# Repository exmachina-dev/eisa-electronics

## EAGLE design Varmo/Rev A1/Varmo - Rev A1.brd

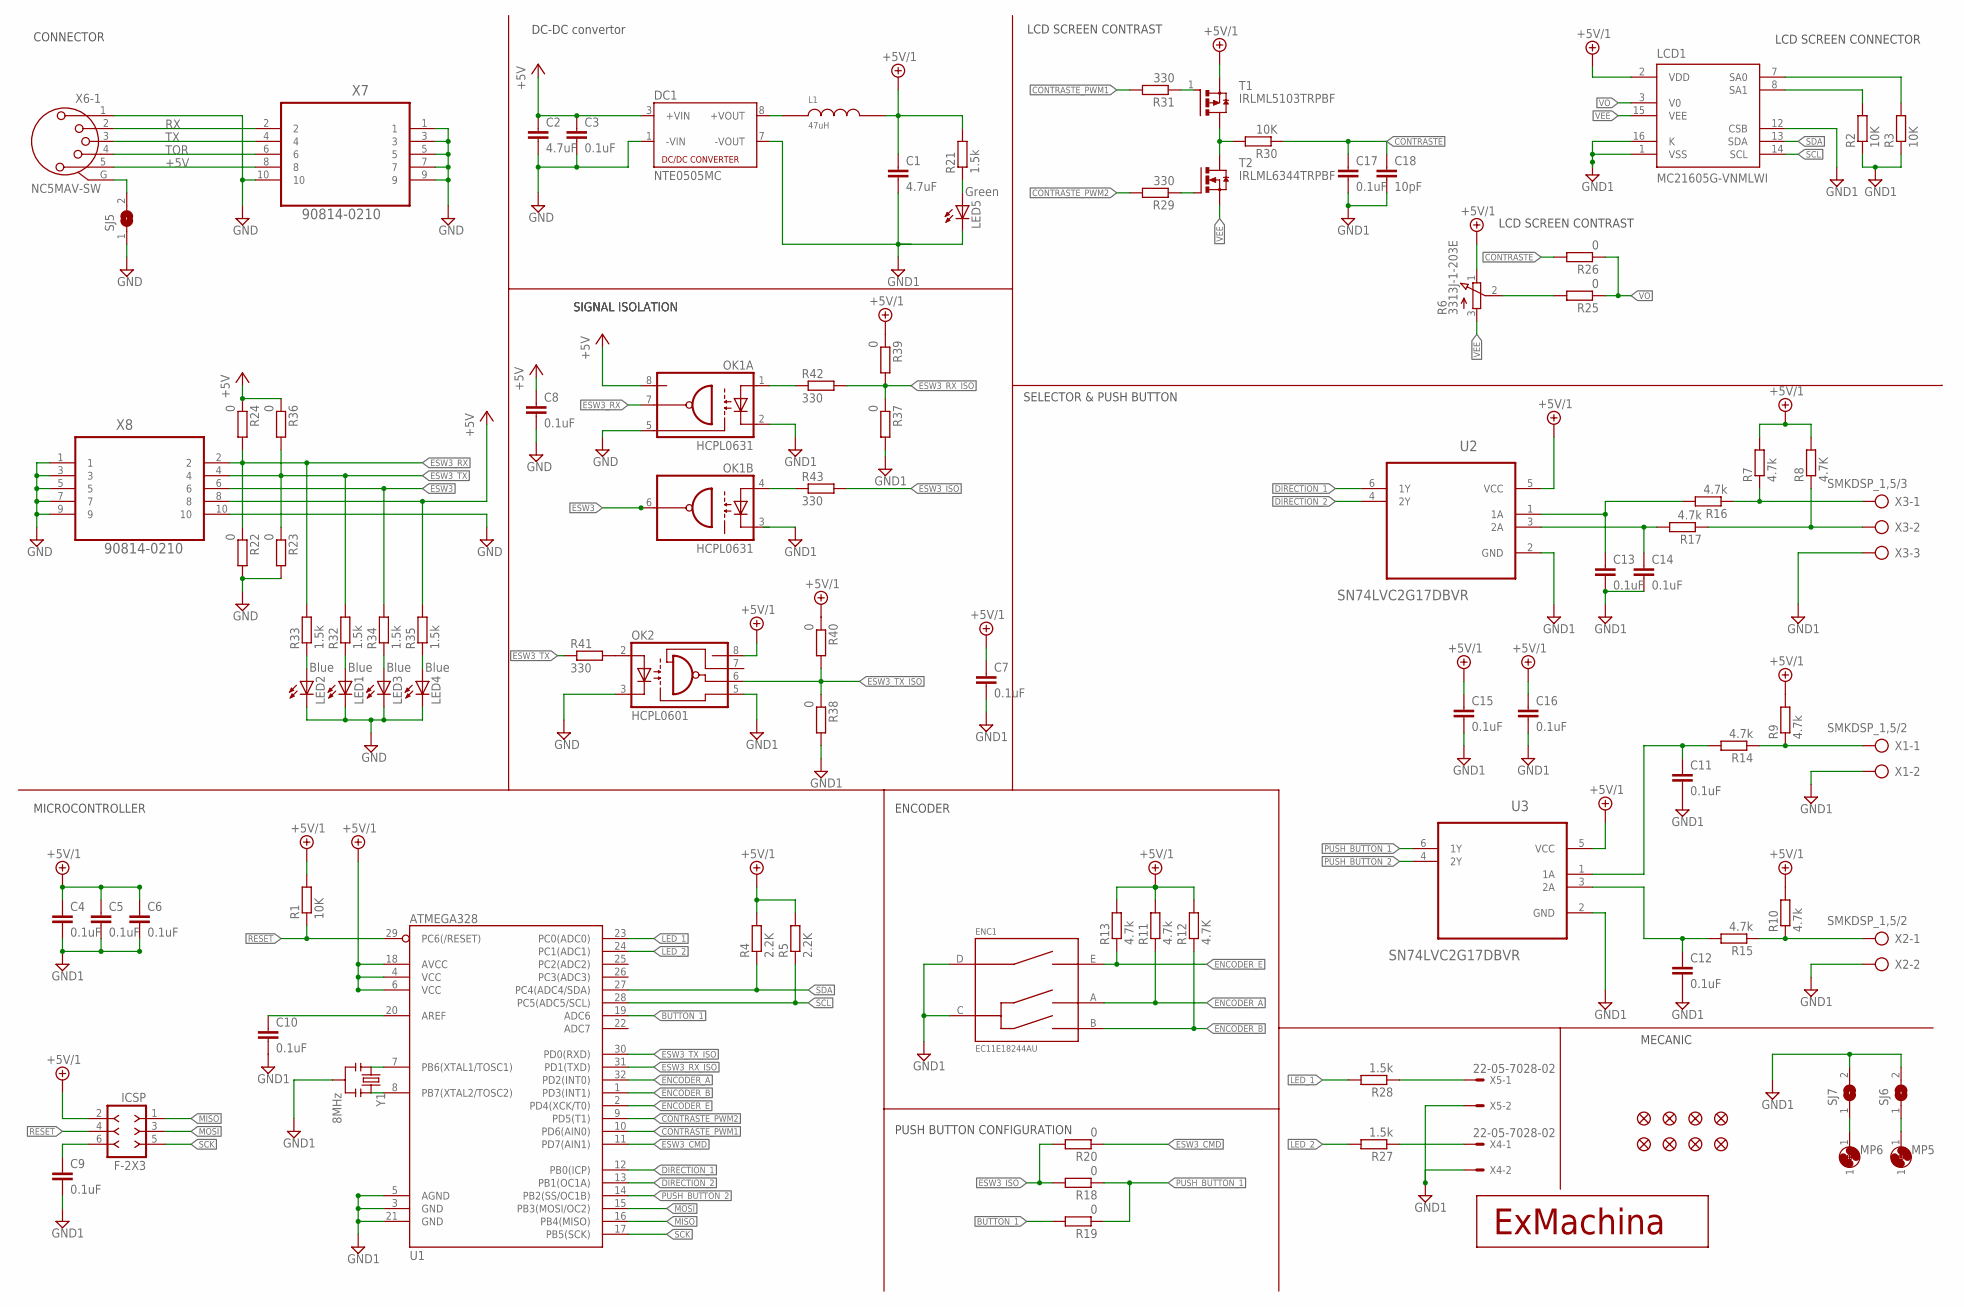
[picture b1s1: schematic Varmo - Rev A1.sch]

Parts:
C1, C2: 4.7uF; C0603; MPN MC0603X475K100CT
C3, C4, C5, C6, C7, C8, C9, C10, C11, C12, C13, C14, C15, C16, C17: 0.1uF; C0603; MPN MC0603B104K160CT
C18: 10pF; C0603; MPN MC0603N100F500CT
DC1: NTE0505MC; NTE; MPN NTE0505MC
ENC1: EC11E18244AU; EC11E
ICSP: F-2X3; DIL-100-2X3; MPN 2213S-06G
JP3, JP4, JP5, JP6, JP7, JP8, JP9, JP10: FIDUCIAL1X2; FIDUCIAL-1X2
L1: 47uH; 8200; MPN 82473C
LCD1: MC21605G-VNMLWI; MC21605G; MPN MC21605G12W-VNMLWI
LED1, LED2, LED3, LED4: Blue; CHIP-LED0603; MPN OVS-0603
LED5: Green; CHIP-LED0603; MPN OVS-0604
MP5, MP6: MOUNT-PAD2.5; P2.5
OK1: HCPL0631; SOIC08
OK2: HCPL0601; SOIC08
R1, R2, R3, R30: 10K; R0603; MPN MCMR06X1002FTL
R4, R5: 2.2K; R0603; MPN MCMR06X2201FTL
R6: 3313J-1-203E; 3313J; MPN 3313J-1-203E
R7, R9, R10, R11, R13, R14, R15, R16, R17: 4.7k; R0603; MPN MCMR06X4701FTL
R8, R12: 4.7K; R0603; MPN MCMR06X4701FTL
R18, R19, R20, R22, R23, R24, R25, R26, R36, R37, R38, R39, R40: 0; R0603; MPN MCMR06X000 PTL
R21, R27, R28, R32, R33, R34, R35: 1.5k; R0603; MPN MCMR06X1501FTL
R29, R31: 330; R0603; MPN MCMR06X3300FTL
R41, R42, R43: 330; R0603; MPN MCMR06X000 PTL
SJ5, SJ6, SJ7: SJ
T1: IRLML5103TRPBF; SOT95P240X112-3N; MPN IRLML5103TRPBF
T2: IRLML6344TRPBF; SOT95P240X112-3N
U1: ATMEGA328; TQFP32-08; MPN ATMEGA328P-AUR
U2, U3: SN74LVC2G17DBVR; SOT95P280X145-6N
U$6: EXMACHINA-LOGO-NAME; EXM-LOGO-BASELINE
X1, X2: SMKDSP_1,5/2
X3: SMKDSP_1,5/3
X4, X5: 22-05-7028-02; 7395-02; MPN 22-05-7028
X6: NC5MAV-SW
X7, X8: 90814-0210; MOLEX_90814-0210
Y1: 8MHz; RESONATOR-SMD; MPN CSTCE8M00G55Z-R0

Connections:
+5V: C2.1, C3.1, C8.1, DC1.3 (+VIN), OK1.8 (VCC), R24.1, R35.2, R36.1, X6.5, X7.8, X8.8
+5V/1: C1.1, C4.1, C5.1, C6.1, C7.1, C15.1, C16.1, ICSP.2, L1.2, LCD1.2 (VDD), OK2.8 (VCC), R1.2, R4.2, R5.2, R6.1 (E), R7.2, R8.2, R9.2, R10.2, R11.2, R12.2, R13.2, R21.2, R39.1, R40.1, T1.2 (S), U1.4 (VCC), U1.6 (VCC), U1.18 (AVCC), U2.5 (VCC), U3.5 (VCC)
BUTTON_1: R19.2, U1.19 (ADC6)
CONTRASTE: C17.1, C18.1, R26.2, R30.1
CONTRASTE_PWM1: R31.2, U1.10 (PD6(AIN0))
CONTRASTE_PWM2: R29.2, U1.9 (PD5(T1))
DIRECTION_1: U1.12 (PB0(ICP)), U2.6 (1Y)
DIRECTION_2: U1.13 (PB1(OC1A)), U2.4 (2Y)
ENCODER_A: ENC1.A, R11.1, U1.32 (PD2(INT0))
ENCODER_B: ENC1.B, R12.1, U1.1 (PD3(INT1))
ENCODER_E: ENC1.E, R13.1, U1.2 (PD4(XCK/T0))
ESW3: OK1.6 (VO2), R34.2, X8.6
ESW3_CMD: R20.1, U1.11 (PD7(AIN1))
ESW3_ISO: R18.2, R20.2, R43.2
ESW3_RX: OK1.7 (VO), R22.1, R24.2, R33.2, X8.2
ESW3_RX_ISO: R37.1, R39.2, R42.2, U1.31 (PD1(TXD))
ESW3_TX: R23.1, R32.2, R36.2, R41.1, X8.4
ESW3_TX_ISO: OK2.6 (VO), R38.1, R40.2, U1.30 (PD0(RXD))
GND: C2.2, C3.2, C8.2, DC1.1 (-VIN), LED1.C, LED2.C, LED3.C, LED4.C, OK1.5 (GND), OK2.3 (C), R22.2, R23.2, SJ5.1, X6.1, X7.1, X7.3, X7.5, X7.7, X7.9, X7.10, X8.1, X8.3, X8.5, X8.7, X8.9, X8.10
GND1: C1.2, C4.2, C5.2, C6.2, C7.2, C9.2, C10.2, C11.2, C12.2, C13.2, C14.2, C15.2, C16.2, C17.2, C18.2, DC1.7 (-VOUT), ENC1.C, ENC1.D, LCD1.1 (VSS), LCD1.12 (CSB), LCD1.16 (K), LED5.C, OK1.2 (C1), OK2.5 (GND), R2.1, R3.1, R37.2, R38.2, SJ6.2, SJ7.2, U1.3 (GND), U1.5 (AGND), U1.21 (GND), U2.2 (GND), U3.2 (GND), X1.2, X2.2, X3.3, X4.2, X5.2, Y1.2
LED_1: R28.2, U1.23 (PC0(ADC0))
LED_2: R27.2, U1.24 (PC1(ADC1))
MISO: ICSP.1, U1.16 (PB4(MISO))
MOSI: ICSP.3, U1.15 (PB3(MOSI/OC2))
unnamed: DC1.8 (+VOUT), L1.1
unnamed: U1.7 (PB6(XTAL1/TOSC1)), Y1.1
unnamed: U1.8 (PB7(XTAL2/TOSC2)), Y1.3
unnamed: C9.1, ICSP.6
unnamed: C10.1, U1.20 (AREF)
unnamed: R10.1, R15.1, X2.1
unnamed: R9.1, R14.1, X1.1
unnamed: R7.1, R16.1, X3.1
unnamed: R8.1, R17.1, X3.2
unnamed: C13.1, R16.2, U2.1 (1A)
unnamed: C14.1, R17.2, U2.3 (2A)
unnamed: C12.1, R15.2, U3.3 (2A)
unnamed: C11.1, R14.2, U3.1 (1A)
unnamed: R6.2 (S), R25.2
unnamed: R27.1, X4.1
unnamed: R28.1, X5.1
unnamed: R29.1, T2.1 (G)
unnamed: R30.2, T1.3 (D), T2.3 (D)
unnamed: SJ5.2, X6.G
unnamed: R31.1, T1.1 (G)
unnamed: LCD1.8 (SA1), R2.2
unnamed: LCD1.7 (SA0), R3.2
unnamed: LED1.A, R32.1
unnamed: LED2.A, R33.1
unnamed: LED3.A, R34.1
unnamed: LED4.A, R35.1
unnamed: LED5.A, R21.1
unnamed: OK1.1 (A1), R42.1
unnamed: OK1.4 (A2), R43.1
unnamed: OK2.2 (A), R41.2
unnamed: MP5.1, SJ6.1
unnamed: MP6.1, SJ7.1
PUSH_BUTTON_1: R18.1, R19.1, U3.6 (1Y)
PUSH_BUTTON_2: U1.14 (PB2(SS/OC1B)), U3.4 (2Y)
RESET: ICSP.4, R1.1, U1.29 (PC6(/RESET))
RX: X6.2, X7.2
SCK: ICSP.5, U1.17 (PB5(SCK))
SCL: LCD1.14 (SCL), R5.1, U1.28 (PC5(ADC5/SCL))
SDA: LCD1.13 (SDA), R4.1, U1.27 (PC4(ADC4/SDA))
TOR: X6.4, X7.6
TX: X6.3, X7.4
VEE: LCD1.15 (VEE), R6.3 (A), T2.2 (S)
VO: LCD1.3 (V0), R25.1, R26.1

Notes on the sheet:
LCD SCREEN CONNECTOR
SIGNAL ISOLATION
DC-DC convertor
LCD SCREEN CONTRAST
MICROCONTROLLER
ENCODER
PUSH BUTTON CONFIGURATION
MECANIC
SELECTOR & PUSH BUTTON
CONNECTOR

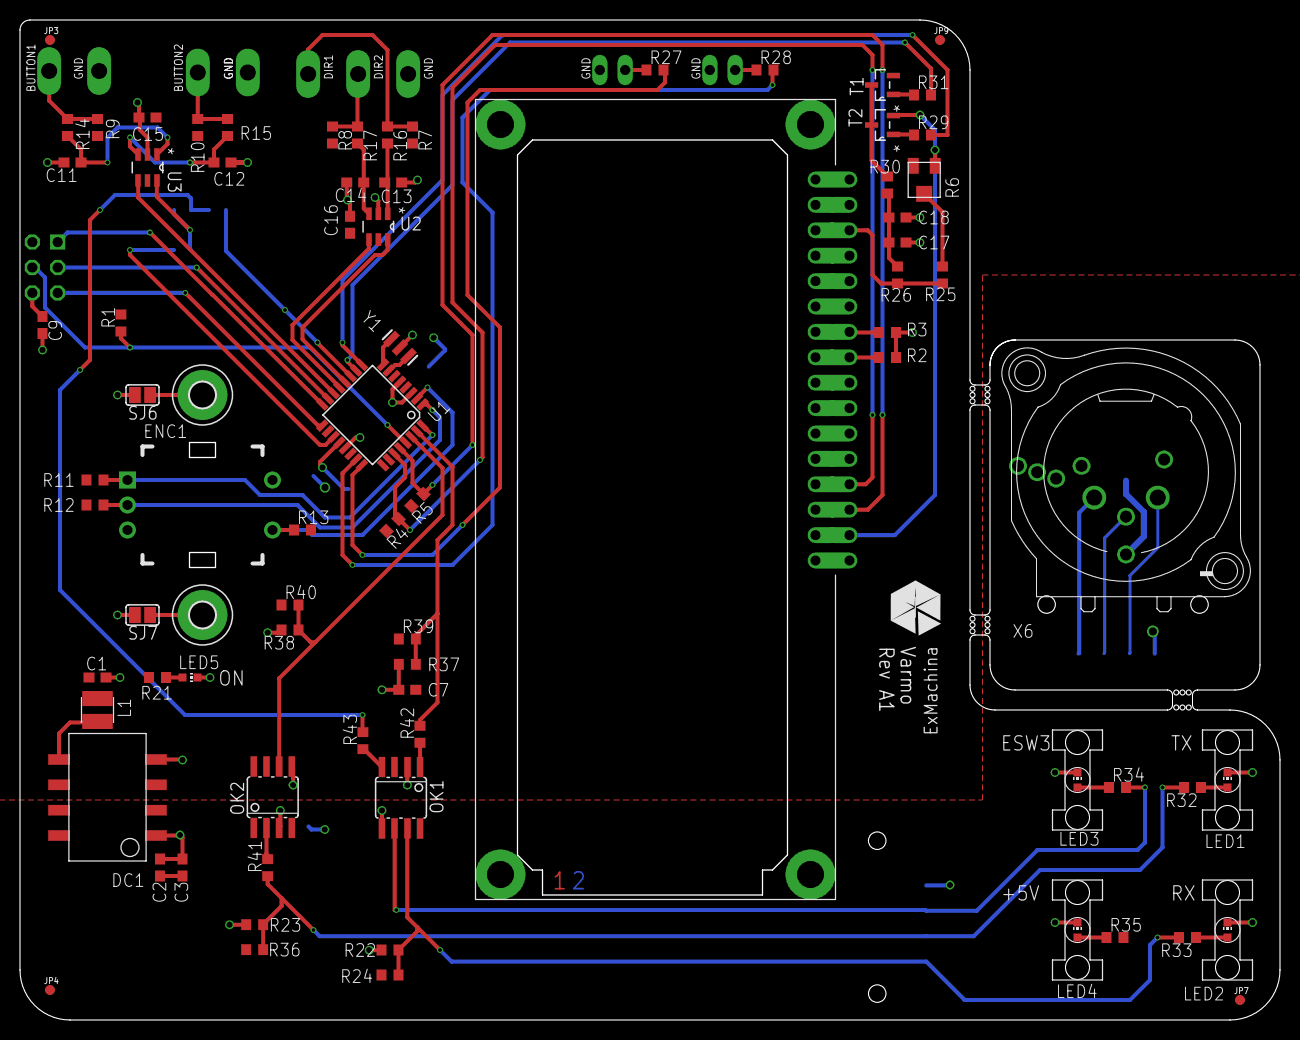
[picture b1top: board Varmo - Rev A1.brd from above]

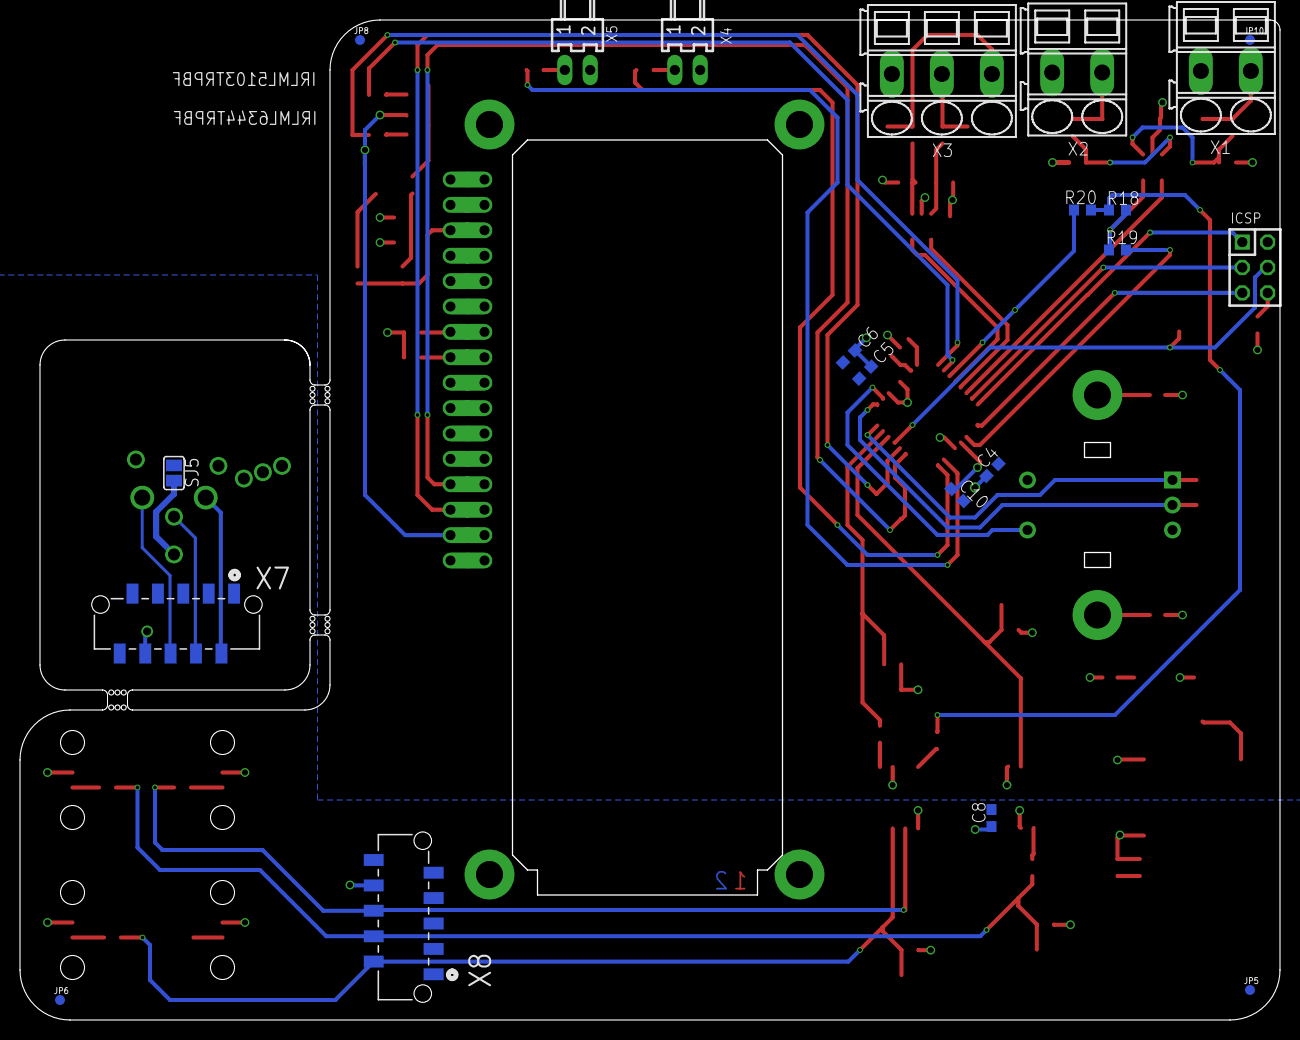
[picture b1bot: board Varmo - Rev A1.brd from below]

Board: 2 copper layers, 126.0 x 100.0 mm, 106 parts (21 on the bottom side), 67 nets.

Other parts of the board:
U$1: A4L-LOC
U$2, U$3, U$4, U$5: 1275.100

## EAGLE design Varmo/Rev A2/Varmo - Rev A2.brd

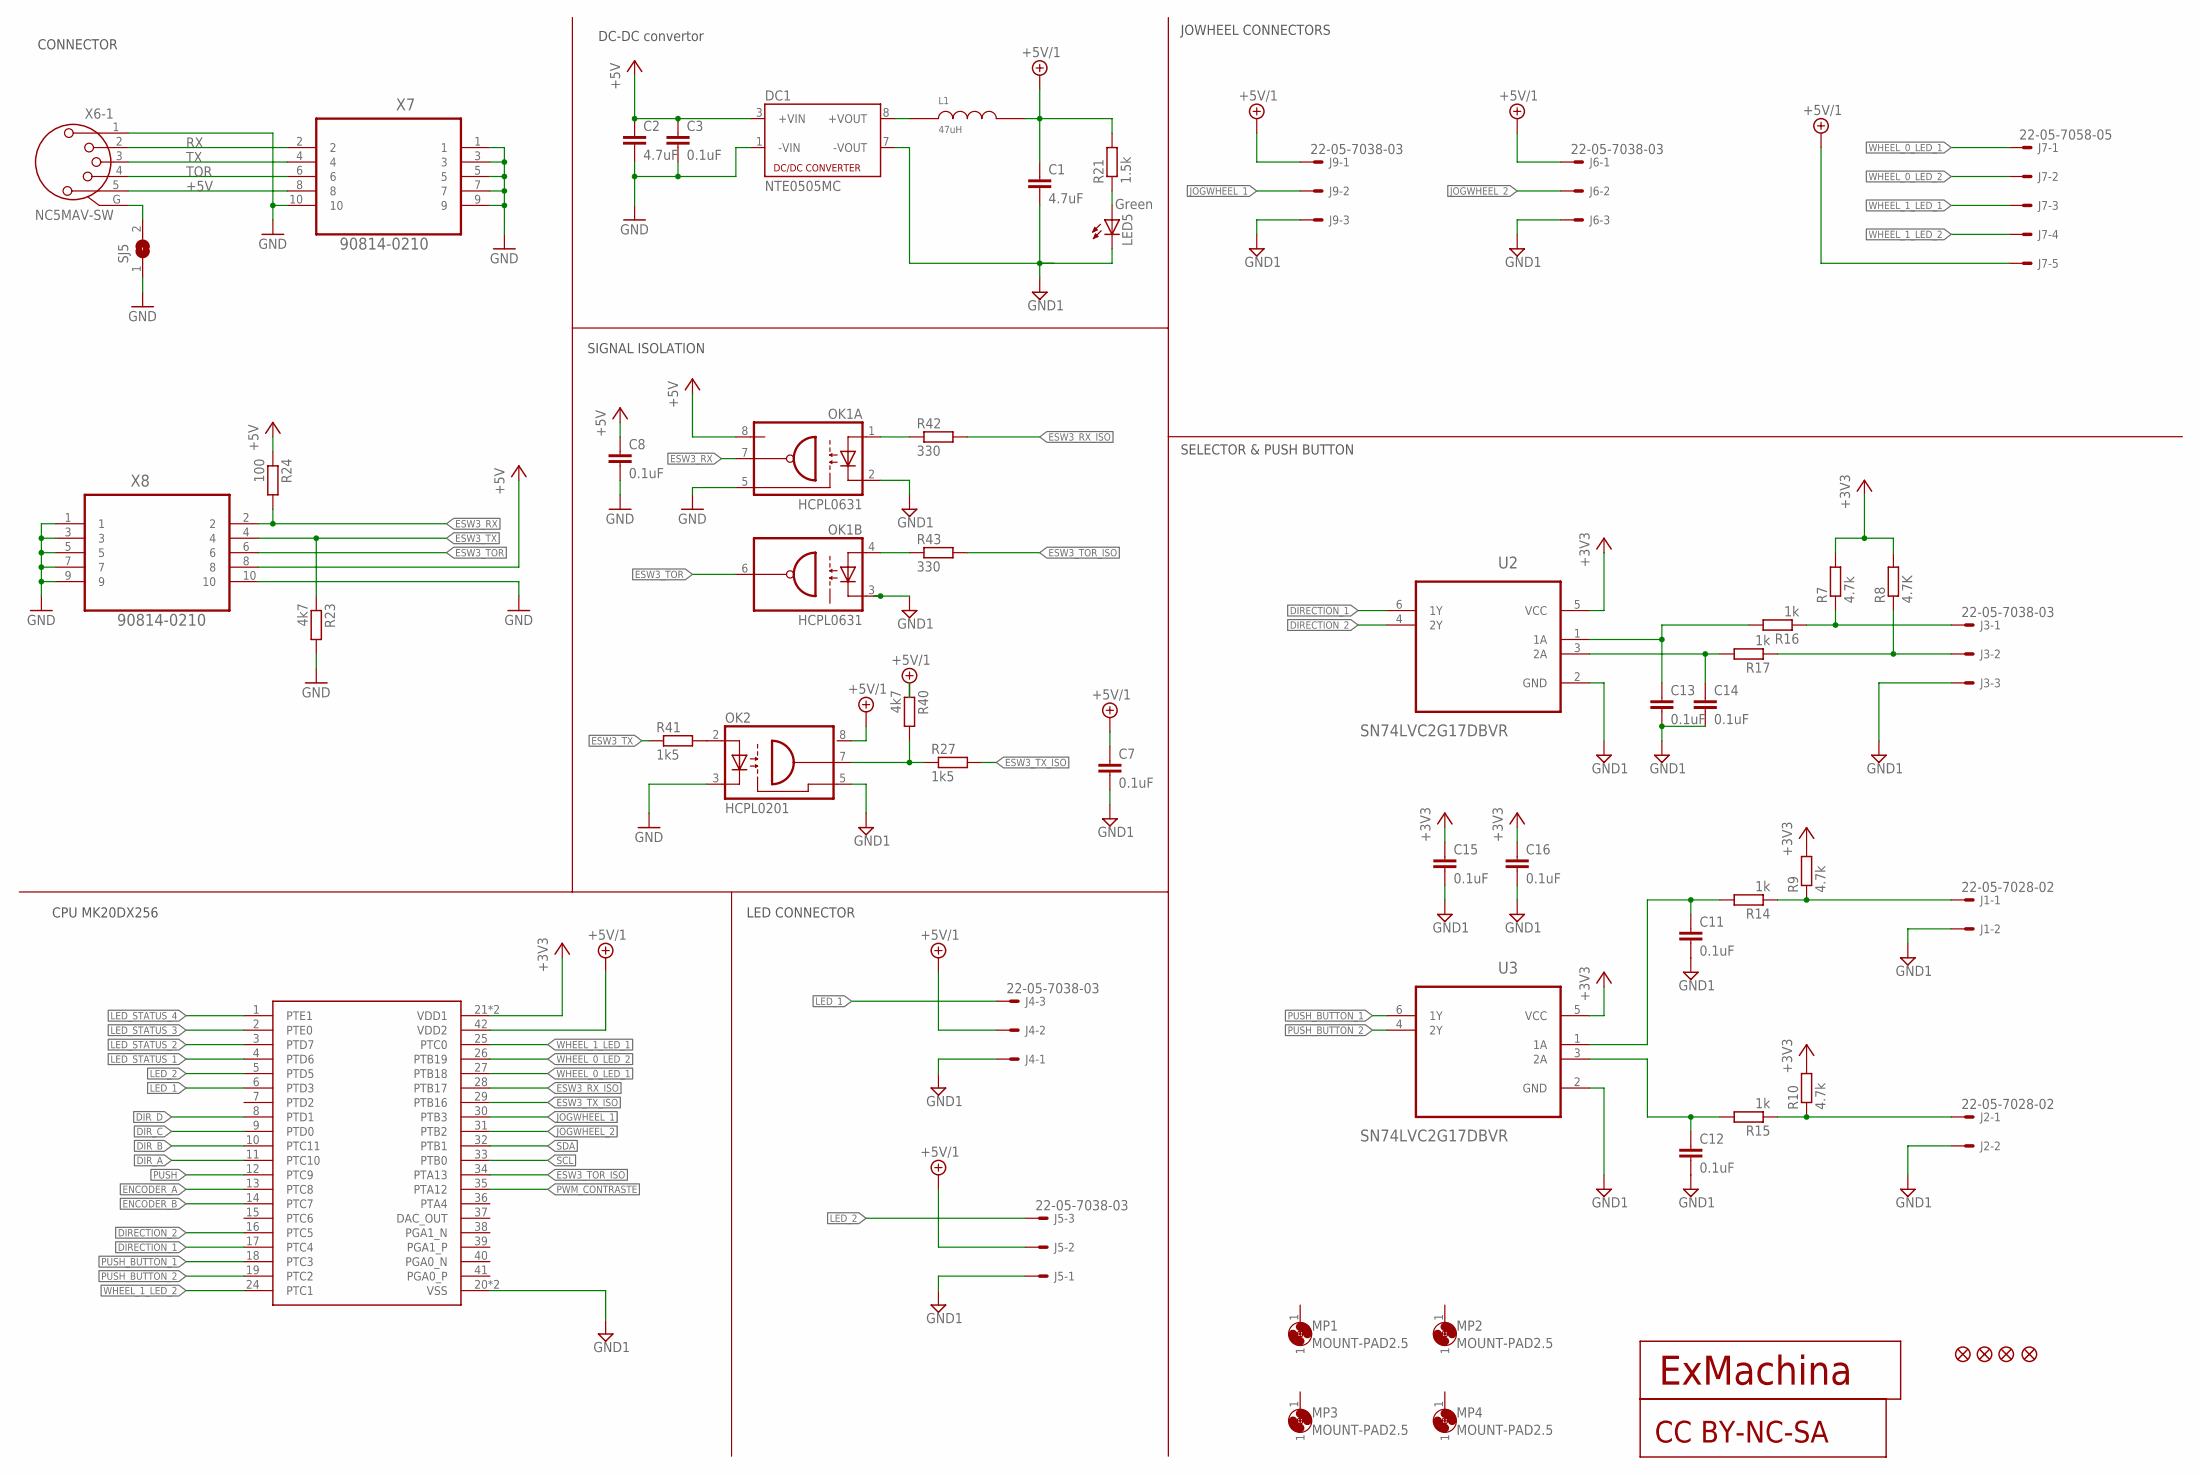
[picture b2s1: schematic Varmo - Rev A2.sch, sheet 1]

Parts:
C1, C2: 4.7uF; C0603; MPN MC0603X475K100CT
C3, C7, C8, C11, C12, C13, C14, C15, C16: 0.1uF; C0603; MPN MC0603B104K160CT
DC1: NTE0505MC; NTE; MPN NTE0505MC
J1, J2: 22-05-7028-02; 7395-02
J3, J4, J5, J6, J9: 22-05-7038-03; 7395-03
J7: 22-05-7058-05; 7395-05
JP1, JP2, JP3, JP4: FIDUCIAL1X2; FIDUCIAL-1X2
L1: 47uH; 8200; MPN 82473C
LED5: Green; CHIP-LED0603; MPN OVS-0604
MP1, MP2, MP3, MP4: MOUNT-PAD2.5; P2.5
OK1: HCPL0631; SOIC08
OK2: HCPL0201; SOIC08
R7, R9, R10: 4.7k; R0603; MPN MCMR06X4701FTL
R8: 4.7K; R0603; MPN MCMR06X4701FTL
R14, R15, R16, R17: 1k; R0603; MPN MCMR06X4701FTL
R21: 1.5k; R0603; MPN MCMR06X1501FTL
R23, R40: 4k7; R0603; MPN MCMR06X000 PTL
R24: 100; R0603; MPN MCMR06X000 PTL
R27, R41: 1k5; R0603; MPN MCMR06X000 PTL
R42, R43: 330; R0603; MPN MCMR06X000 PTL
SJ5: SJ
U2, U3: SN74LVC2G17DBVR; SOT95P280X145-6N
U8: M20DX256; MK_CUSTOM
U$1: CC-BY-NC-SA
U$6: EXMACHINA-LOGO-NAME; EXM-LOGO-BASELINE
X6: NC5MAV-SW
X7, X8: 90814-0210; MOLEX_90814-0210

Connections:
+3V3: C15.1, C16.1, R7.2, R8.2, R9.2, R10.2, U2.5 (VCC), U3.5 (VCC), U8.21 (VDD1), U8.22 (VDD1); also elsewhere on the board
+5V: C2.1, C3.1, C8.1, DC1.3 (+VIN), OK1.8 (VCC), R24.1, X6.5, X7.8, X8.8
+5V/1: C1.1, C7.1, J4.2, J5.2, J6.1, J7.5, J9.1, L1.2, OK2.8 (VCC), R21.2, R40.1, U8.42 (VDD2); also elsewhere on the board
DIRECTION_1: U2.6 (1Y), U8.17 (PTC4)
DIRECTION_2: U2.4 (2Y), U8.16 (PTC5)
DIR_A: U8.11 (PTC10); also elsewhere on the board
DIR_B: U8.10 (PTC11); also elsewhere on the board
DIR_C: U8.9 (PTD0); also elsewhere on the board
DIR_D: U8.8 (PTD1); also elsewhere on the board
ENCODER_A: U8.13 (PTC8); also elsewhere on the board
ENCODER_B: U8.14 (PTC7); also elsewhere on the board
ESW3_RX: OK1.7 (VO), R24.2, X8.2
ESW3_RX_ISO: R42.2, U8.28 (PTB17)
ESW3_TOR: OK1.6 (VO2), X8.6
ESW3_TOR_ISO: R43.2, U8.34 (PTA13)
ESW3_TX: R23.1, R41.1, X8.4
ESW3_TX_ISO: R27.2, U8.29 (PTB16)
GND: C2.2, C3.2, C8.2, DC1.1 (-VIN), OK1.5 (GND), OK2.3 (C), R23.2, SJ5.1, X6.1, X7.1, X7.3, X7.5, X7.7, X7.9, X7.10, X8.1, X8.3, X8.5, X8.7, X8.9, X8.10
GND1: C1.2, C7.2, C11.2, C12.2, C13.2, C14.2, C15.2, C16.2, DC1.7 (-VOUT), J1.2, J2.2, J3.3, J4.1, J5.1, J6.3, J9.3, LED5.C, OK1.2 (C1), OK1.3 (C2), OK2.5 (GND), U2.2 (GND), U3.2 (GND), U8.20 (VSS), U8.23 (VSS); also elsewhere on the board
JOGWHEEL_1: J9.2, U8.30 (PTB3)
JOGWHEEL_2: J6.2, U8.31 (PTB2)
LED_1: J4.3, U8.6 (PTD3)
LED_2: J5.3, U8.5 (PTD5)
LED_STATUS_1: U8.4 (PTD6); also elsewhere on the board
LED_STATUS_2: U8.3 (PTD7); also elsewhere on the board
LED_STATUS_3: U8.2 (PTE0); also elsewhere on the board
LED_STATUS_4: U8.1 (PTE1); also elsewhere on the board
unnamed: DC1.8 (+VOUT), L1.1
unnamed: J2.1, R10.1, R15.1
unnamed: J1.1, R9.1, R14.1
unnamed: J3.1, R7.1, R16.1
unnamed: J3.2, R8.1, R17.1
unnamed: C13.1, R16.2, U2.1 (1A)
unnamed: C14.1, R17.2, U2.3 (2A)
unnamed: C12.1, R15.2, U3.3 (2A)
unnamed: C11.1, R14.2, U3.1 (1A)
unnamed: OK2.7 (VO), R27.1, R40.2
unnamed: SJ5.2, X6.G
unnamed: LED5.A, R21.1
unnamed: OK1.1 (A1), R42.1
unnamed: OK1.4 (A2), R43.1
unnamed: OK2.2 (A), R41.2
PUSH: U8.12 (PTC9); also elsewhere on the board
PUSH_BUTTON_1: U3.6 (1Y), U8.18 (PTC3)
PUSH_BUTTON_2: U3.4 (2Y), U8.19 (PTC2)
PWM_CONTRASTE: U8.35 (PTA12); also elsewhere on the board
RX: X6.2, X7.2
SCL: U8.33 (PTB0); also elsewhere on the board
SDA: U8.32 (PTB1); also elsewhere on the board
TOR: X6.4, X7.6
TX: X6.3, X7.4
WHEEL_0_LED_1: J7.1, U8.27 (PTB18)
WHEEL_0_LED_2: J7.2, U8.26 (PTB19)
WHEEL_1_LED_1: J7.3, U8.25 (PTC0)
WHEEL_1_LED_2: J7.4, U8.24 (PTC1)

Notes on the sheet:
SIGNAL ISOLATION
DC-DC convertor
SELECTOR & PUSH BUTTON
CONNECTOR
JOWHEEL CONNECTORS
CPU MK20DX256
LED CONNECTOR

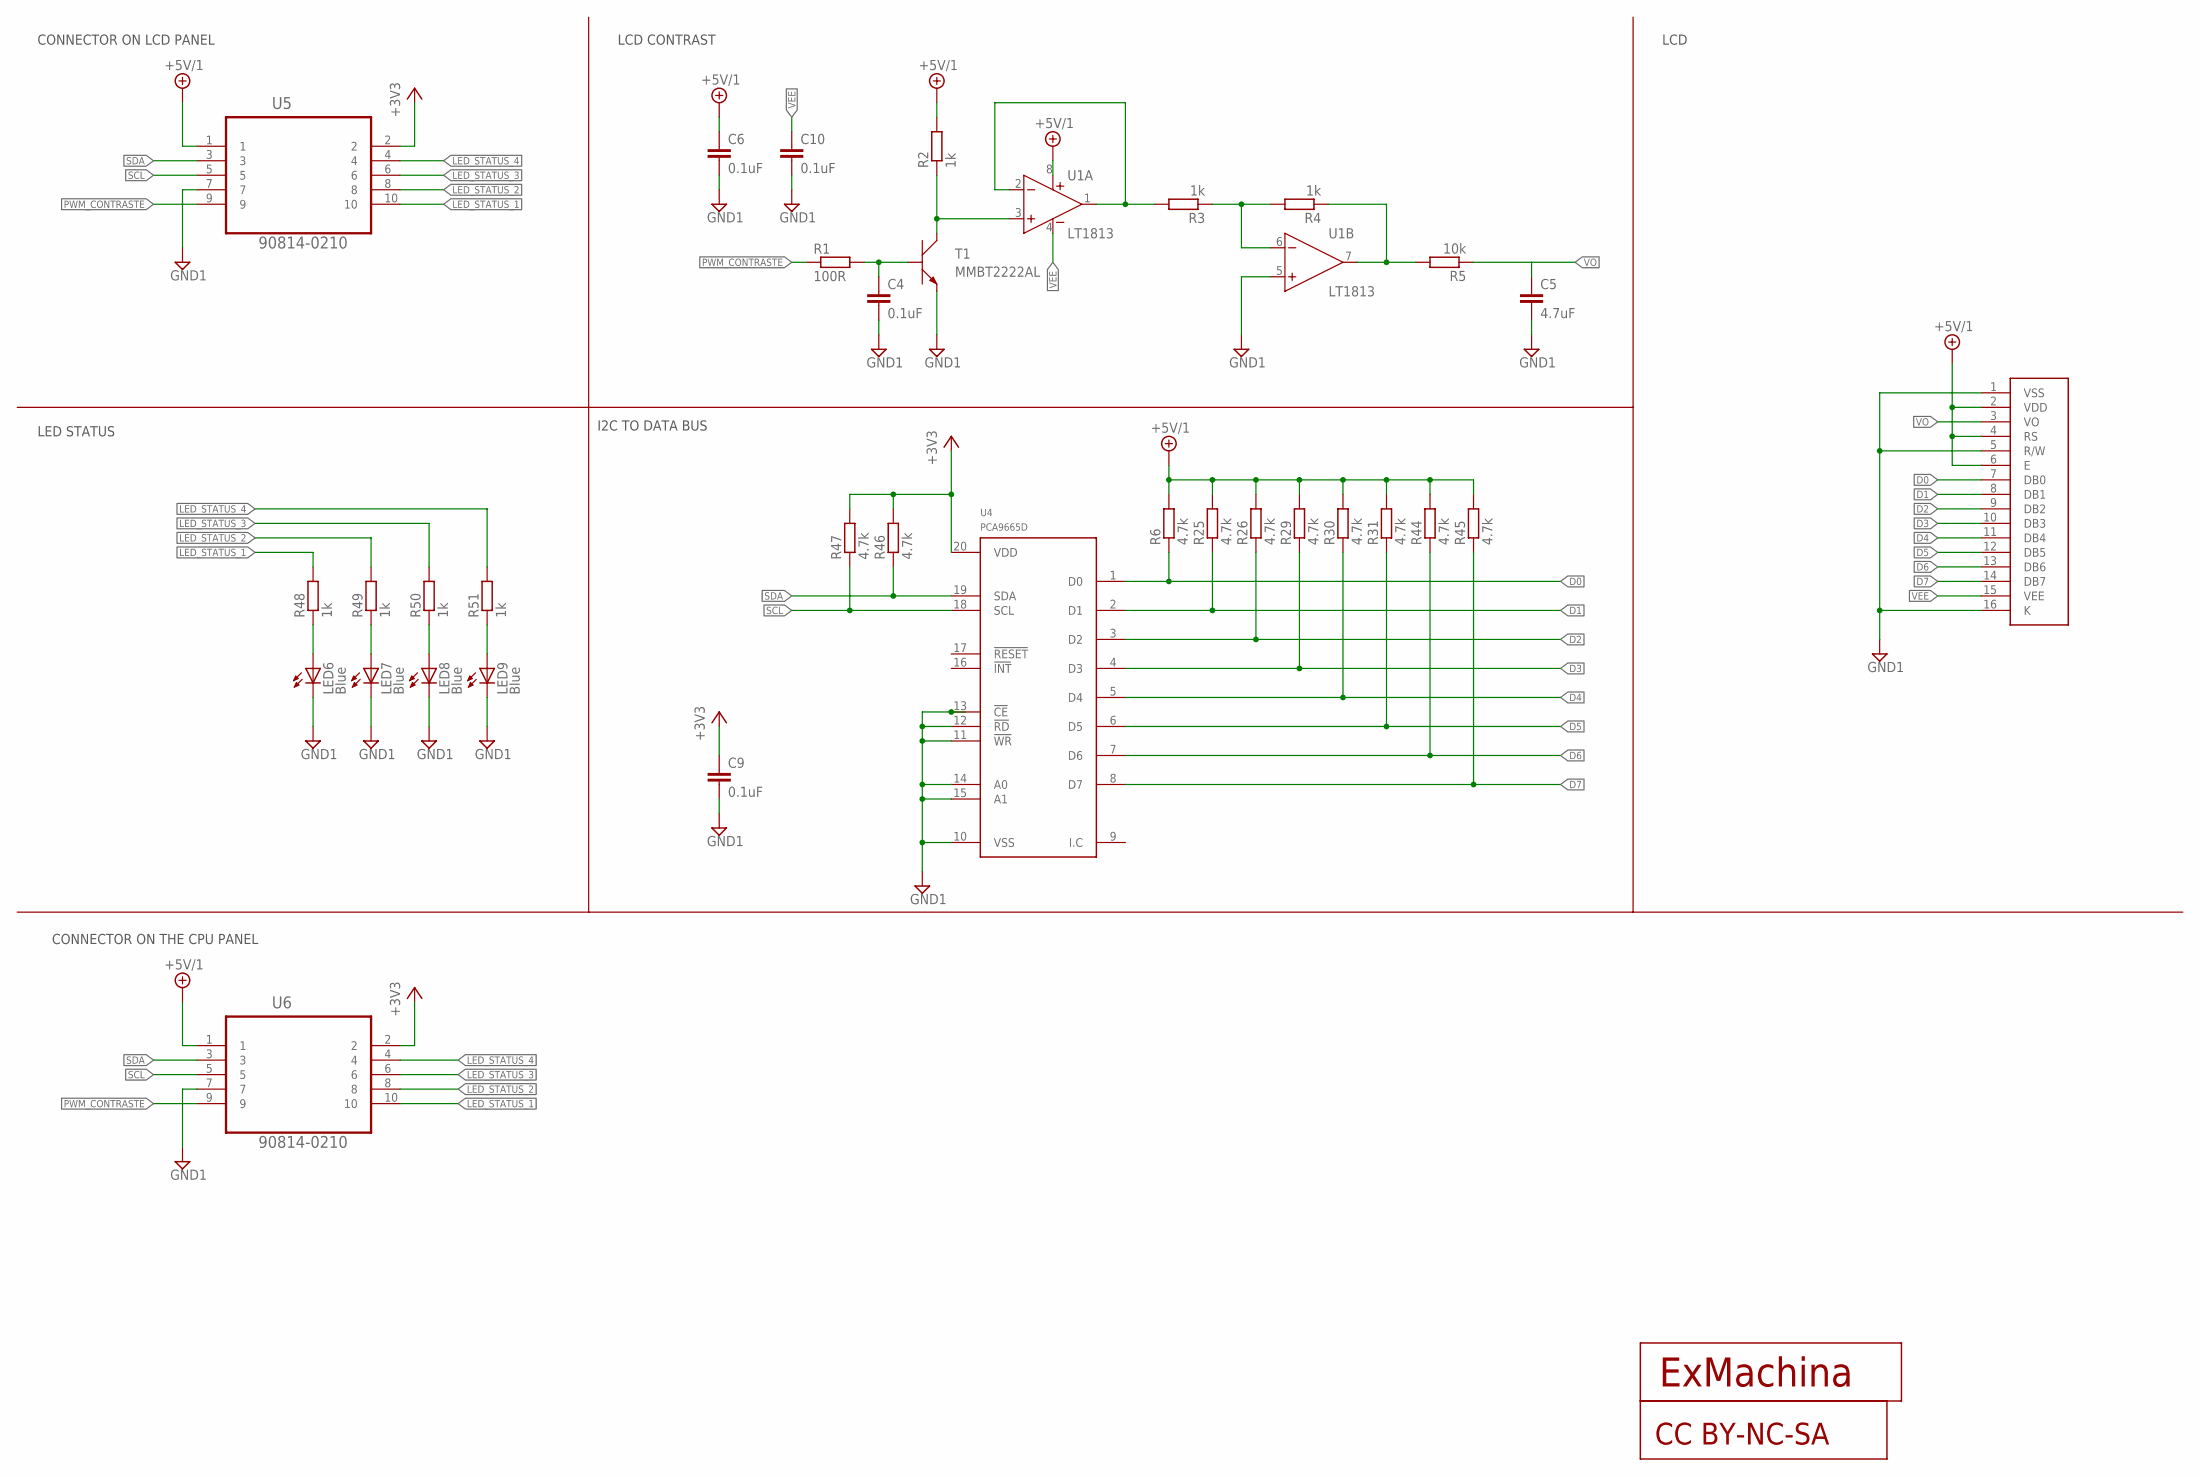
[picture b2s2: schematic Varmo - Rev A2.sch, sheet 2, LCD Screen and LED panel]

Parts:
C4, C6, C9, C10: 0.1uF; C0603
C5: 4.7uF; C0603
LCD1: MC41605A12W; CONNECTOR
LED6, LED7, LED8, LED9: Blue; CHIP-LED0603
R1: 100R; R0603
R2, R3, R4, R48, R49, R50, R51: 1k; R0603
R5: 10k; R0603
R6, R25, R26, R29, R30, R31, R44, R45, R46, R47: 4.7k; R0603
T1: MMBT2222AL; SOT−23
U1: LT1813; S8
U4: PCA9665D; SOT163-1
U5, U6: 90814-0210; MOLEX_90814-0210
U$5: CC-BY-NC-SA
U$7: EXMACHINA-LOGO-NAME; EXM-LOGO-BASELINE

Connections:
+3V3: C9.1, R46.2, R47.2, U4.20 (VDD), U5.2, U6.2; also elsewhere on the board
+5V/1: C6.1, LCD1.2 (VDD), LCD1.4 (RS), LCD1.6 (E), R2.2, R6.2, R25.2, R26.2, R29.2, R30.2, R31.2, R44.2, R45.2, U1.8 (V+), U5.1, U6.1; also elsewhere on the board
D0: LCD1.7 (DB0), R6.1, U4.1 (D0)
D1: LCD1.8 (DB1), R25.1, U4.2 (D1)
D2: LCD1.9 (DB2), R26.1, U4.3 (D2)
D3: LCD1.10 (DB3), R29.1, U4.4 (D3)
D4: LCD1.11 (DB4), R30.1, U4.5 (D4)
D5: LCD1.12 (DB5), R31.1, U4.6 (D5)
D6: LCD1.13 (DB6), R44.1, U4.7 (D6)
D7: LCD1.14 (DB7), R45.1, U4.8 (D7)
GND1: C4.2, C5.2, C6.2, C9.2, C10.2, LCD1.1 (VSS), LCD1.5 (R/W), LCD1.16 (K), LED6.C, LED7.C, LED8.C, LED9.C, T1.2 (E), U1.5 (IN+), U4.10 (VSS), U4.11 (!WR), U4.12 (!RD), U4.13 (!CE), U4.14 (A0), U4.15 (A1), U5.7, U6.7; also elsewhere on the board
LED_STATUS_1: R48.2, U5.10, U6.10; also elsewhere on the board
LED_STATUS_2: R49.2, U5.8, U6.8; also elsewhere on the board
LED_STATUS_3: R50.2, U5.6, U6.6; also elsewhere on the board
LED_STATUS_4: R51.2, U5.4, U6.4; also elsewhere on the board
unnamed: C4.1, R1.2, T1.1 (B)
unnamed: R2.1, T1.3 (C), U1.3 (IN+)
unnamed: LED6.A, R48.1
unnamed: R3.2, U1.1 (OUT), U1.2 (IN-)
unnamed: R3.1, R4.2, U1.6 (IN-)
unnamed: R4.1, R5.2, U1.7 (OUT)
unnamed: LED7.A, R49.1
unnamed: LED8.A, R50.1
unnamed: LED9.A, R51.1
PWM_CONTRASTE: R1.1, U5.9, U6.9; also elsewhere on the board
SCL: R47.1, U4.18 (SCL), U5.5, U6.5; also elsewhere on the board
SDA: R46.1, U4.19 (SDA), U5.3, U6.3; also elsewhere on the board
VEE: C10.1, LCD1.15 (VEE), U1.4 (V-)
VO: C5.1, LCD1.3 (VO), R5.1

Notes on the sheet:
LCD CONTRAST
CONNECTOR ON LCD PANEL
LED STATUS
I2C TO DATA BUS
LCD
CONNECTOR ON THE CPU PANEL

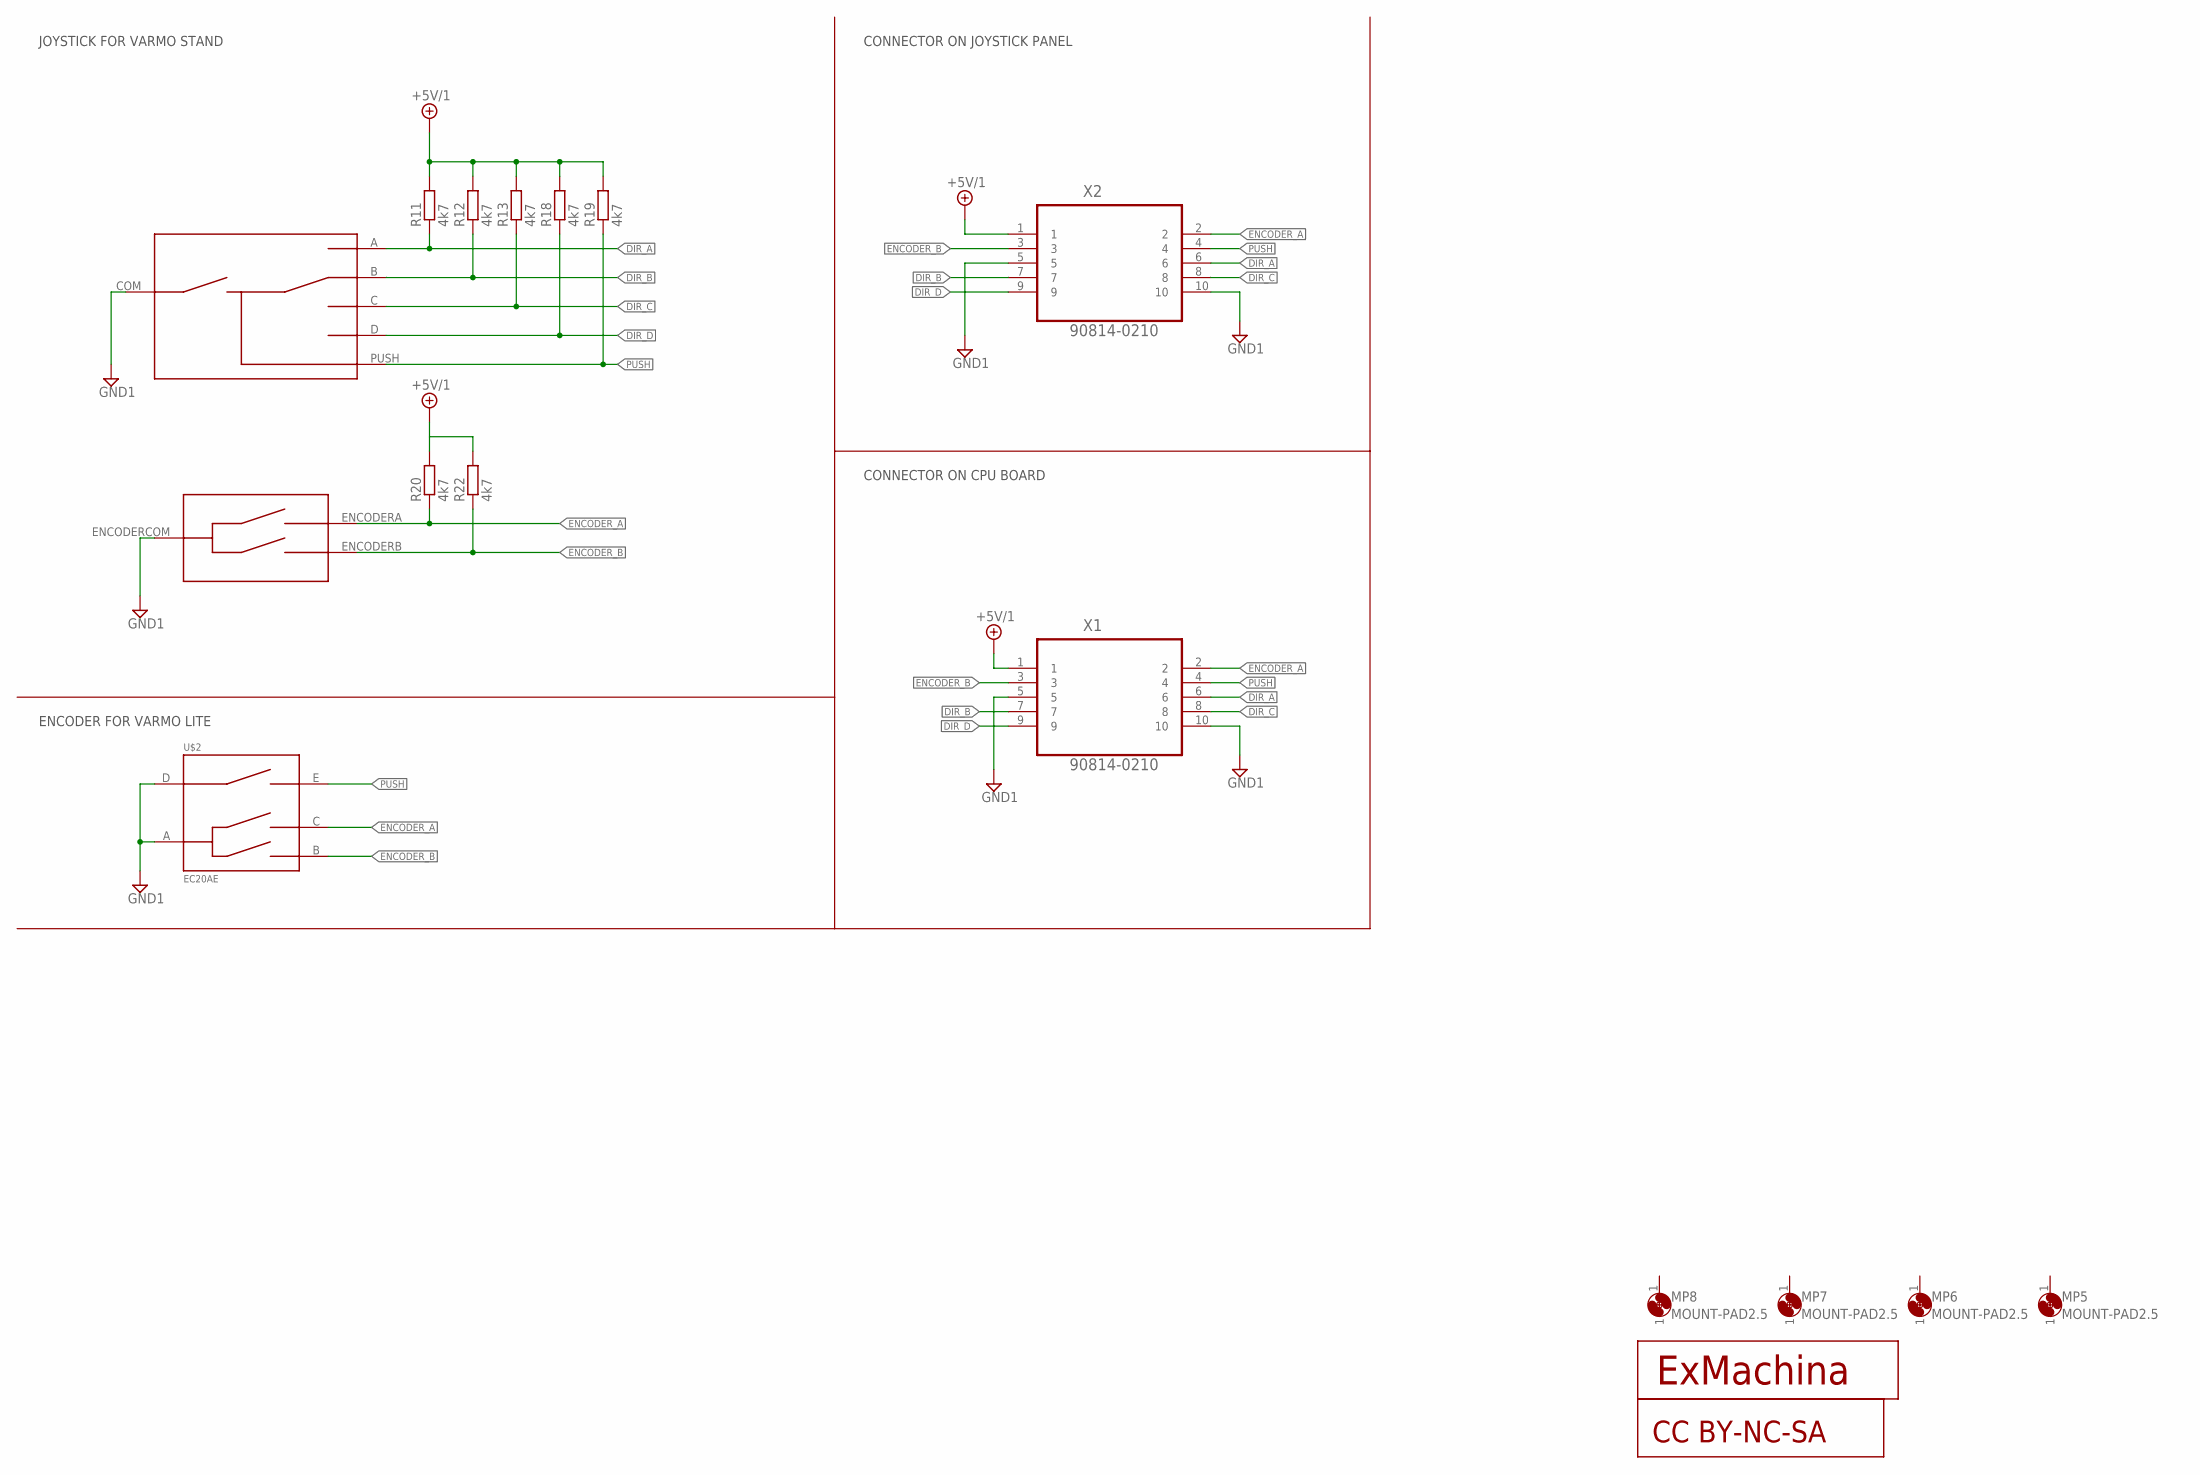
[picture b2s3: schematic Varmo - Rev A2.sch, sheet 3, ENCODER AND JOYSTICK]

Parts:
ENC1: RKJXTF42001; RKJXT1F
MP5, MP6, MP7, MP8: MOUNT-PAD2.5; P2.5
R11, R12, R13, R18, R19, R20, R22: 4k7; R0603; MPN MCMR06X000 PTL
U$2: EC20AE; EC20A
U$3: EXMACHINA-LOGO-NAME; EXM-LOGO-BASELINE
U$4: CC-BY-NC-SA
X1, X2: 90814-0210; MOLEX_90814-0210

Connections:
+5V/1: R11.2, R12.2, R13.2, R18.2, R19.2, R20.2, R22.2, X1.1, X2.1; also elsewhere on the board
DIR_A: ENC1.A, R11.1, X1.6, X2.6; also elsewhere on the board
DIR_B: ENC1.B, R12.1, X1.7, X2.7; also elsewhere on the board
DIR_C: ENC1.C, R13.1, X1.8, X2.8; also elsewhere on the board
DIR_D: ENC1.D, R18.1, X1.9, X2.9; also elsewhere on the board
ENCODER_A: ENC1.ENCODERA (A), R20.1, U$2.C (ENCODER_A), X1.2, X2.2; also elsewhere on the board
ENCODER_B: ENC1.ENCODERB (B), R22.1, U$2.B (ENCODER_B), X1.3, X2.3; also elsewhere on the board
GND1: ENC1.COM, ENC1.ENCODERCOM (COM), U$2.A (COM), U$2.D (COM_PUSH), X1.5, X1.10, X2.5, X2.10; also elsewhere on the board
PUSH: ENC1.PUSH, R19.1, U$2.E (PUSH), X1.4, X2.4; also elsewhere on the board

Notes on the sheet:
JOYSTICK FOR VARMO STAND
ENCODER FOR VARMO LITE
CONNECTOR ON CPU BOARD
CONNECTOR ON JOYSTICK PANEL
